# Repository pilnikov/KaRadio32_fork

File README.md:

# KaRadio32_fork
modifed files from karadio32 https://github.com/karawin/Ka-Radio32
for use with TTGO TM Music.

Since version 1.5. - end of support. For history only!
Please use original files with ttgotm.bin config and ST7789V (199) display.

Файлы для проекта Karadio32 https://github.com/karawin/Ka-Radio32
адаптированные под использование с платой TTGO TM Music
https://ru.aliexpress.com/item/Ttgo-2-4-PCM5102A-SD-ESP32-WiFi-Bluetooth/32848882218.html?spm=a2g0s.9042311.0.0.BYS264

Русский язык поддерживается!

Начиная с версии 1.5 потеряло актуальность. Теперь можно грузить оригинальную прошивку и специальный файл конфигурации ttgotm.bin из папочки \boards\build у автора(или тут). Дисплей в новых версиях - ST7789V (199)

Тут пока оставлю для истории. 

P.S. В папочку \boards буду складывать различные конфиги (под разные платы)
схема подключения в файликах с расширением .csv. Соответсвующие .csv бинарники лежат в подпапке \build. Грузить бинарник можно отдельно от основной прошивки по адресу 0x3a2000

пример 

строка P_TOUCH_CS,data,u8,16
означает, что пин CS тачскрина (для экранов с тачскринами, еще может обозначаться как t_cs) нужно подключить к GPIO16

строка P_BACKLIGHT,data,u8,255
означает, что управление подсветкой экрана не используется (значение 255) и экран будет светиться постоянно.

чтобы сделать .bin из .csv без msys
http://totel.kusto.com.ru:18888/karadio/

если установлен python:
1. заходите в папку с файлом вашей конфигурации. 
2. копируете туда файлик nvs_partition_gen.py. 
3. запускаете командную строку (cmd)
4. копируете строчку python nvs_partition_gen.py имя_конфига.csv имя_бинарника.bin 0x2000 (где вместо имя_конфига.csv подставляеете свой .csv (например ttgotm.csv (должен лежать в этой же папке)), а вместо имя_бинарника.bin произвольное имя файла которое потом будет заливаться (например build/ttgotm.bin (создаст подпапку /buld, а в неё положит файл ttgotm.bin ))

Теперь поддерживаются модули A1S от Aithinker!

Все исходники https://github.com/pilnikov/Ka_mod.
Бинарник собран при помощи Ninja & Cmake на базе IDF 4.1 (на IDF 5.x пока не работает)

Хорошая инструкция от Игоря Шерстюка (aka nadim)
https://www.drive2.ru/b/487463808323813881/

Еще инструкции от пользователя maleksm с форума Arduino 
http://arduino.ru/forum/proekty/wi-fi-internet-radio?page=104#comment-443847

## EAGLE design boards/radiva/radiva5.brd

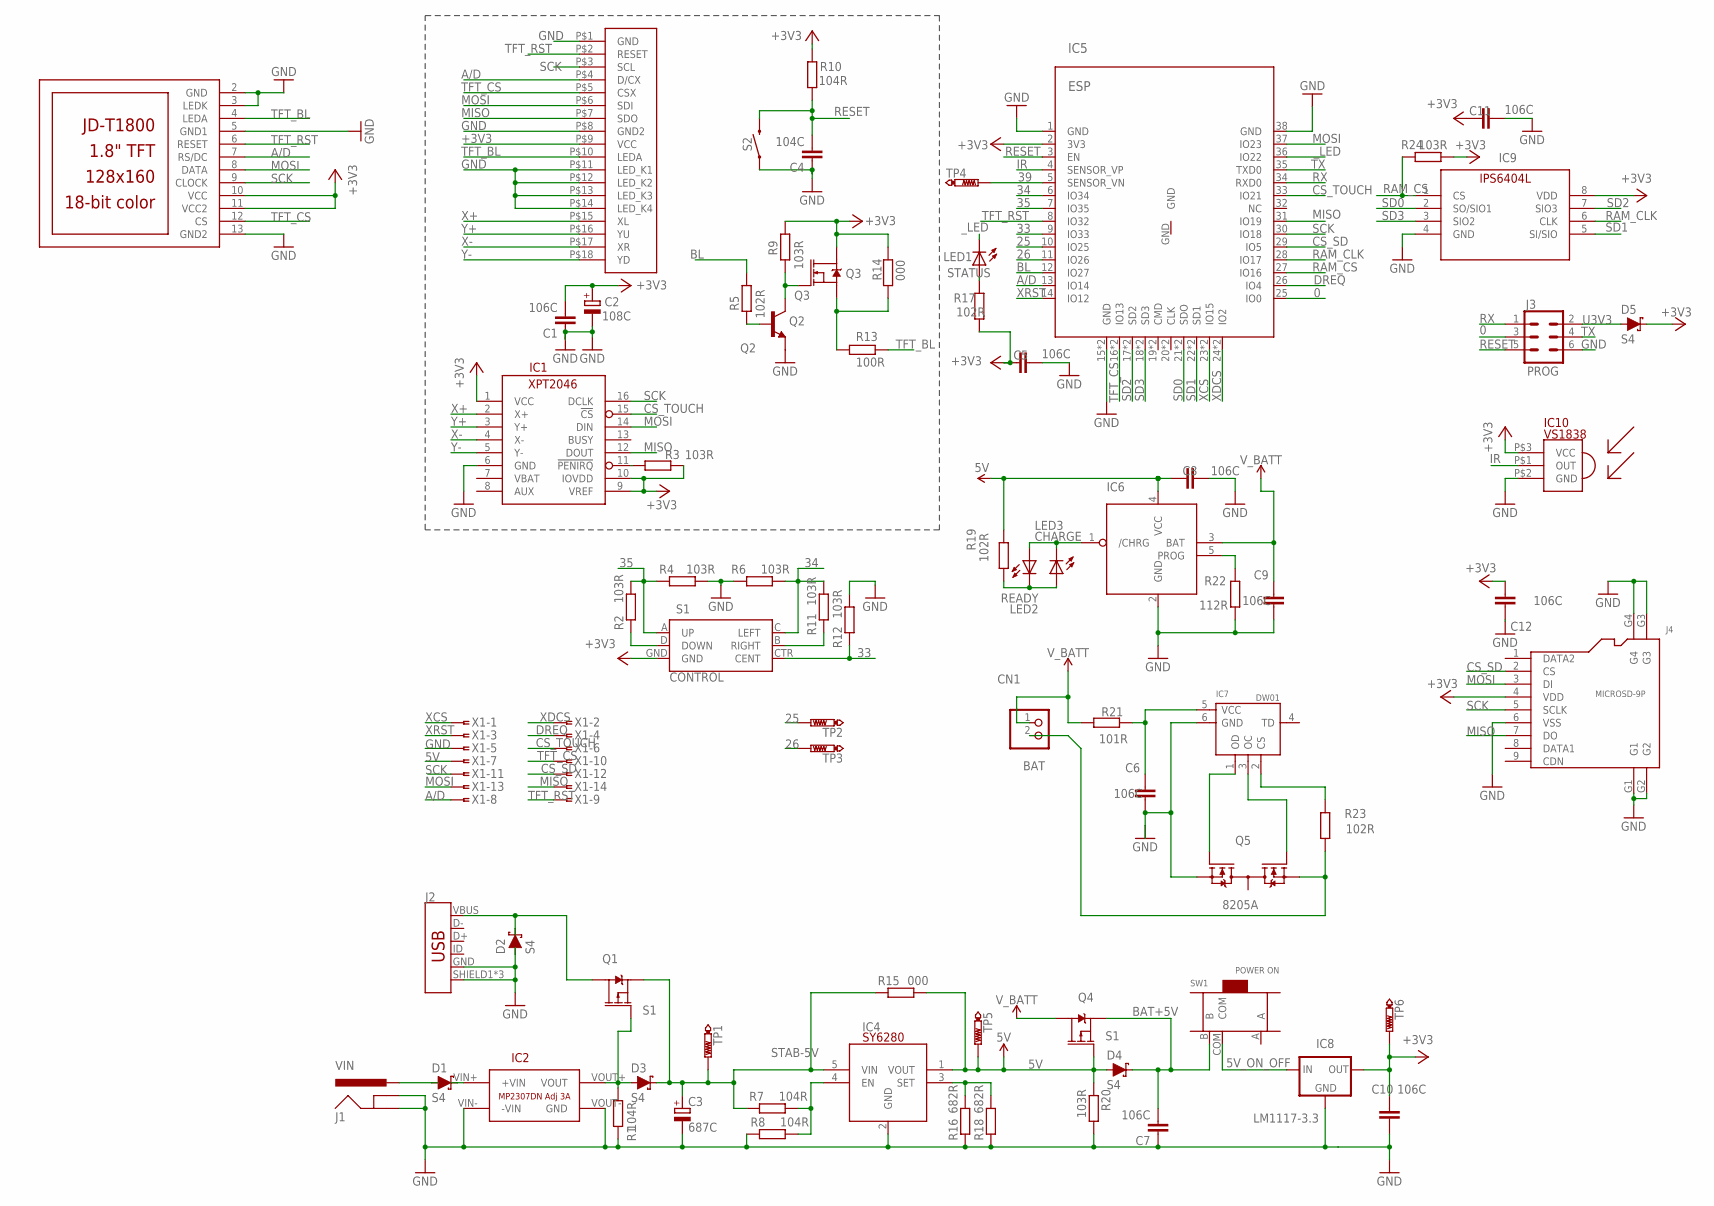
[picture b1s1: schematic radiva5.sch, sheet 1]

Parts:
C1, C5, C6, C7, C8, C9, C10, C11, C12: 106C; 0603-CAP
C2: 108C; E5-8,5
C3: 687C; E5-8,5
C4: 104C; 0603-CAP
CN1: BAT; JST-PH-2-SMT
D1, D2, D3, D4, D5: S4; SOD-323
IC1: TOUCH; TSSOP16-0.65-5X4.4MM
IC2: DC-DC 5V; DC-DC_MP2307DN
IC3: TFT-DISPLAY-2.8
IC4: SY6280; SOT23-5
IC5: ESP; ESP-WROOM-WROOVER-32
IC6: LT4; SOT23-5
IC7: DW01; SOT-23-6
IC8: LM1117-3.3; SOT223
IC9: SRAM; SO-08
IC10: VS1838; IR
J1: VIN; POWER_JACK_PTH_LOCK
J2: USB_MICRO-B_FEMALE-SMT; USB-B-MICRO-SMD
J3: PROG; 2X3
J4: MICROSD-9P; MICRO-SD9+4P-SMD-16.1X14.5X1.85MM
LCD1: TFT-DISPLAY-1.8; JD-T1800
LED1: STATUS; LED-0603
LED2: READY; LED-0603
LED3: CHARGE; LED-0603
Q1, Q4: S1; SOT23-3
Q2: Q2; SOT23-3
Q3: Q3; SOT23-3
Q5: 8205A; TSSOP-8
R1, R7, R8, R10: 104R; R0603
R2, R3, R4, R6, R9, R11, R12, R20, R24: 103R; R0603
R5, R17, R19, R23: 102R; R0603
R13: 100R; R0603
R14, R15: 000; R0603
R16, R18: 682R; R0603
R21: 101R; R0603
R22: 112R; R0603
S1: CONTROL; JOYSTICK_MINI
S2: RESET; TACTILE_SWITCH_PTH_8.0MM
SW1: POWER ON; SW7-SMD-L6.7X2.7X3.2MM
TP1: STAB 5V; P1-13
TP2: 25; B1,27
TP3: 26; B1,27
TP4: 39; B1,27
TP5: 5V; P1-13
TP6: 3.3V; P1-13
X1: FSIDE-14

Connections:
0: IC5.25 (IO0), J3.3
5V: C8.1, D4.+ (A), IC4.1 (VOUT), IC6.4 (VCC), Q4.1 (G), R15.2, R19.2, R20.1, TP5.TP, X1.7
5V_ON_OFF: IC8.3 (IN), SW1.COM
25: IC5.10 (IO25), TP2.TP
26: IC5.11 (IO26), TP3.TP
33: IC5.9 (IO33), R12.1, S1.CTR (CENT)
34: IC5.6 (IO34), R6.2, R11.2, S1.C (LEFT)
35: IC5.7 (IO35), R2.2, R4.1, S1.A (UP)
39: IC5.5 (SENSOR_VN), TP4.TP
+3V3: C1.2, C2.+, C5.1, C10.2, C11.1, C12.1, D5.- (C), IC1.1 (VCC), IC1.9 (VREF), IC1.10 (IOVDD), IC3.P$9 (VCC), IC5.2 (3V3), IC8.2 (OUT), IC8.4 (OUT), IC9.8 (VDD), IC10.P$3 (VCC), J4.4 (VDD), LCD1.10 (VCC), LCD1.11 (VCC2), Q3.3 (D), R3.1, R9.1, R10.1, R14.1, R17.1, R24.1, S1.GND, TP6.TP; also elsewhere on the board
A/D: IC3.P$4 (D/CX), IC5.13 (IO14), LCD1.7 (RS/DC), X1.8
BAT+5V: C7.2, D4.- (C), Q4.2 (S), SW1.B
BL: IC5.12 (IO27), R5.1
CHARGE: IC6.1 (/CHRG), LED2.A, LED3.C
CS_SD: IC5.29 (IO5), J4.2 (CS), X1.12
CS_TOUCH: IC1.15 (!CS), IC5.33 (IO21), X1.6
DREQ: IC5.26 (IO4), X1.4; also elsewhere on the board
FUSE_EN: IC4.4 (EN), R7.2, R8.1
FUSE_SET: IC4.3 (SET), R16.2, R18.2
GND: C1.1, C2.-, C3.-, C4.1, C5.2, C6.1, C7.1, C8.2, C9.1, C10.1, C11.2, C12.2, D2.+ (A), IC1.6 (GND), IC2.VIN- (-VIN), IC2.VOUT- (GND), IC3.P$1 (GND), IC3.P$8 (GND2), IC3.P$11 (LED_K1), IC3.P$12 (LED_K2), IC3.P$13 (LED_K3), IC3.P$14 (LED_K4), IC4.2 (GND), IC5.1 (GND), IC5.15 (GND), IC5.38 (GND), IC5.39 (GND), IC6.2 (GND), IC7.6 (GND), IC8.1 (GND), IC9.4 (GND), IC10.P$2 (GND), J1.GND, J1.GNDBREAK, J2.GND, J2.SHIELD1 (SHIELD), J2.SHIELD2 (SHIELD), J2.SHIELD3 (SHIELD), J3.6, J4.6 (VSS), J4.G1, J4.G2, J4.G3, J4.G4, LCD1.2 (GND), LCD1.3 (LEDK), LCD1.5 (GND1), LCD1.13 (GND2), Q2.2 (E), Q5.6 (S2), Q5.7 (S2), R1.2, R4.2, R6.1, R8.2, R12.2, R16.1, R18.1, R20.2, R22.1, S2.1, X1.5; also elsewhere on the board
ICHRG: IC6.5 (PROG), R22.2
IR: IC5.4 (SENSOR_VP), IC10.P$1 (OUT)
MISO: IC1.12 (DOUT), IC3.P$7 (SDO), IC5.31 (IO19), J4.7 (DO), X1.14; also elsewhere on the board
MOSI: IC1.14 (DIN), IC3.P$6 (SDI), IC5.37 (IO23), J4.3 (DI), LCD1.8 (DATA), X1.13; also elsewhere on the board
unnamed: Q2.3 (C), Q3.1 (G), R9.2
unnamed: Q3.2 (S), R13.1, R14.2
unnamed: Q2.1 (B), R5.2
unnamed: LED1.A, R17.2
unnamed: LED2.C, LED3.A, R19.1
unnamed: IC7.3 (OC), Q5.4 (G1)
unnamed: IC7.1 (OD), Q5.5 (G2)
unnamed: C6.2, IC7.5 (VCC), R21.2
unnamed: IC7.2 (CS), R23.2
unnamed: CN1.2 (1), Q5.2 (S1), Q5.3 (S1), R23.1
unnamed: IC1.11 (!PENIRQ), R3.2
unnamed: R11.1, S1.B (RIGHT)
unnamed: R2.1, S1.D (DOWN)
RAM_CLK: IC5.28 (IO17), IC9.6 (CLK)
RAM_CS: IC5.27 (IO16), IC9.1 (CS), R24.2
RESET: C4.2, IC5.3 (EN), J3.5, R10.2, S2.2
RX: IC5.34 (RXD0), J3.1
SCK: IC1.16 (DCLK), IC3.P$3 (SCL), IC5.30 (IO18), J4.5 (SCLK), LCD1.9 (CLOCK), X1.11; also elsewhere on the board
SD0: IC5.21 (SDO), IC5.45 (SDO), IC9.2 (SO/SIO1)
SD1: IC5.22 (SD1), IC5.46 (SD1), IC9.5 (SI/SIO)
SD2: IC5.17 (SD2), IC5.41 (SD2), IC9.7 (SIO3)
SD3: IC5.18 (SD3), IC5.42 (SD3), IC9.3 (SIO2)
STAB-5V: C3.+, D3.- (C), IC4.5 (VIN), Q1.2 (S), R7.1, R15.1, TP1.TP
STAB_5V_OUT: D3.+ (A), IC2.VOUT+ (VOUT), Q1.1 (G), R1.1
TFT_BL: IC3.P$10 (LEDA), LCD1.4 (LEDA), R13.2
TFT_CS: IC3.P$5 (CSX), IC5.16 (IO13), IC5.40 (IO13), LCD1.12 (CS), X1.10
TFT_RST: IC3.P$2 (RESET), IC5.8 (IO32), LCD1.6 (RESET), X1.9
TX: IC5.35 (TXD0), J3.4
U3V3: D5.+ (A), J3.2
VBUS: D2.- (C), J2.VBUS, Q1.3 (D)
VIN+: D1.+ (A), J1.PWR
V_BATT: C9.2, CN1.1 (2), IC6.3 (BAT), Q4.3 (D), R21.1
X+: IC1.2 (X+), IC3.P$15 (XL)
X-: IC1.4 (X-), IC3.P$17 (XR)
XCS: IC5.23 (IO15), IC5.47 (IO15), X1.1; also elsewhere on the board
XDCS: IC5.24 (IO2), IC5.48 (IO2), X1.2; also elsewhere on the board
XRST: IC5.14 (IO12), X1.3; also elsewhere on the board
Y+: IC1.3 (Y+), IC3.P$16 (YU)
Y-: IC1.5 (Y-), IC3.P$18 (YD)
_LED: IC5.36 (IO22), LED1.C
_VIN+: D1.- (C), IC2.VIN+ (+VIN)

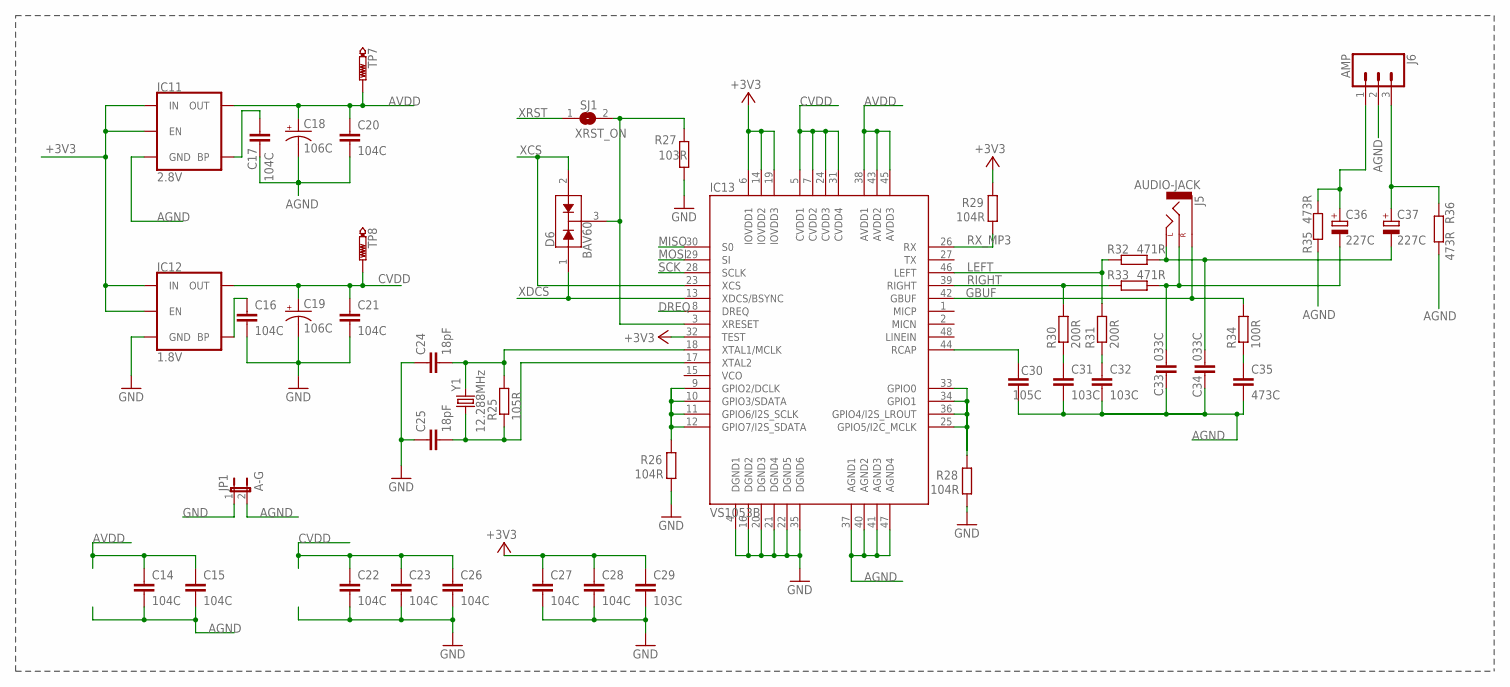
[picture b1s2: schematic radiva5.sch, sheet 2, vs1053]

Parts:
C14, C15, C16, C17, C20, C21, C22, C23, C26, C27, C28: 104C; 0603-CAP
C18, C19: 106C; EIA3216
C24, C25: 18pF; 0603-CAP
C29, C31, C32: 103C; 0603-CAP
C30: 105C; 0603-CAP
C33, C34: 033C; 0603-CAP
C35: 473C; 0603-CAP
C36, C37: 227C; E2,5-6
D6: BAV60; SOT23-3
IC11: 2.8V; SOT23-5
IC12: 1.8V; SOT23-5
IC13: VS1053B; LQFP-48
J5: AUDIO-JACK
J6: AMP; 1X03
JP1: A-G; SJ_2S
R25: 105R; R0603
R26, R28, R29: 104R; R0603
R27: 103R; R0603
R30, R31: 200R; R0603
R32, R33: 471R; R0603
R34: 100R; R0603
R35, R36: 473R; R0603
SJ1: XRST_ON; SJ
TP7: 2.8V; B1,27
TP8: 1.8V; B1,27
Y1: 12.288MHz; HC49U

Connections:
+3V3: C27.1, C28.1, C29.1, IC11.1 (IN), IC11.3 (EN), IC12.1 (IN), IC12.3 (EN), IC13.6 (IOVDD1), IC13.14 (IOVDD2), IC13.19 (IOVDD3), IC13.32 (TEST), R29.2; also elsewhere on the board
AGND: C14.2, C15.2, C17.2, C18.C (-), C20.2, C30.1, C31.2, C32.2, C33.2, C34.2, C35.2, IC11.2 (GND), IC13.37 (AGND1), IC13.40 (AGND2), IC13.41 (AGND3), IC13.47 (AGND4), J6.2, JP1.2, R35.2, R36.1
AMP_L: C36.+, J6.1, R35.1
AMP_R: C37.+, J6.3, R36.2
AVDD: C14.1, C15.1, C18.A (+), C20.1, IC11.5 (OUT), IC13.38 (AVDD1), IC13.43 (AVDD2), IC13.45 (AVDD3), TP7.TP
CVDD: C19.A (+), C21.1, C22.1, C23.1, C26.1, IC12.5 (OUT), IC13.5 (CVDD1), IC13.7 (CVDD2), IC13.24 (CVDD3), IC13.31 (CVDD4), TP8.TP
DREQ: IC13.8 (DREQ); also elsewhere on the board
GBUF: IC13.42 (GBUF), J5.P$3 (SLEEVE), J5.P$4 (SLEEVE), R34.2
GND: C16.2, C19.C (-), C21.2, C22.2, C23.2, C24.1, C25.1, C26.2, C27.2, C28.2, C29.2, IC12.2 (GND), IC13.4 (DGND1), IC13.16 (DGND2), IC13.20 (DGND3), IC13.21 (DGND4), IC13.22 (DGND5), IC13.35 (DGND6), JP1.1, R26.1, R27.1, R28.1; also elsewhere on the board
GPIO_0: IC13.25 (GPIO5/I2C_MCLK), IC13.33 (GPIO0), IC13.34 (GPIO1), IC13.36 (GPIO4/I2S_LROUT), R28.2
GPIO_2: IC13.9 (GPIO2/DCLK), IC13.10 (GPIO3/SDATA), IC13.11 (GPIO6/I2S_SCLK), IC13.12 (GPIO7/I2S_SDATA), R26.2
HP_L: C33.1, C36.-, J5.P$2 (RIGHT), R33.1
HP_R: C34.1, C37.-, J5.P$1 (LEFT), J5.P$5 (LEFT), R32.1
LEFT: IC13.46 (LEFT), R31.2, R32.2
MISO: IC13.30 (S0); also elsewhere on the board
MOSI: IC13.29 (SI); also elsewhere on the board
unnamed: C17.1, IC11.4 (BP)
unnamed: C16.1, IC12.4 (BP)
unnamed: C32.1, R31.1
unnamed: C31.1, R30.1
unnamed: C35.1, R34.1
RCAP: C30.2, IC13.44 (RCAP)
RIGHT: IC13.39 (RIGHT), R30.2, R33.2
RX_MP3: IC13.26 (RX), R29.1
SCK: IC13.28 (SCLK); also elsewhere on the board
XCS: D6.2 (A2), IC13.23 (XCS); also elsewhere on the board
XDCS: D6.1 (A1), IC13.13 (XDCS/BSYNC); also elsewhere on the board
XRESET: D6.3 (COM), IC13.3 (XRESET), R27.2, SJ1.2
XRST: SJ1.1; also elsewhere on the board
XTAL+: C25.2, IC13.17 (XTAL2), R25.1, Y1.1
XTAL-: C24.2, IC13.18 (XTAL1/MCLK), R25.2, Y1.2

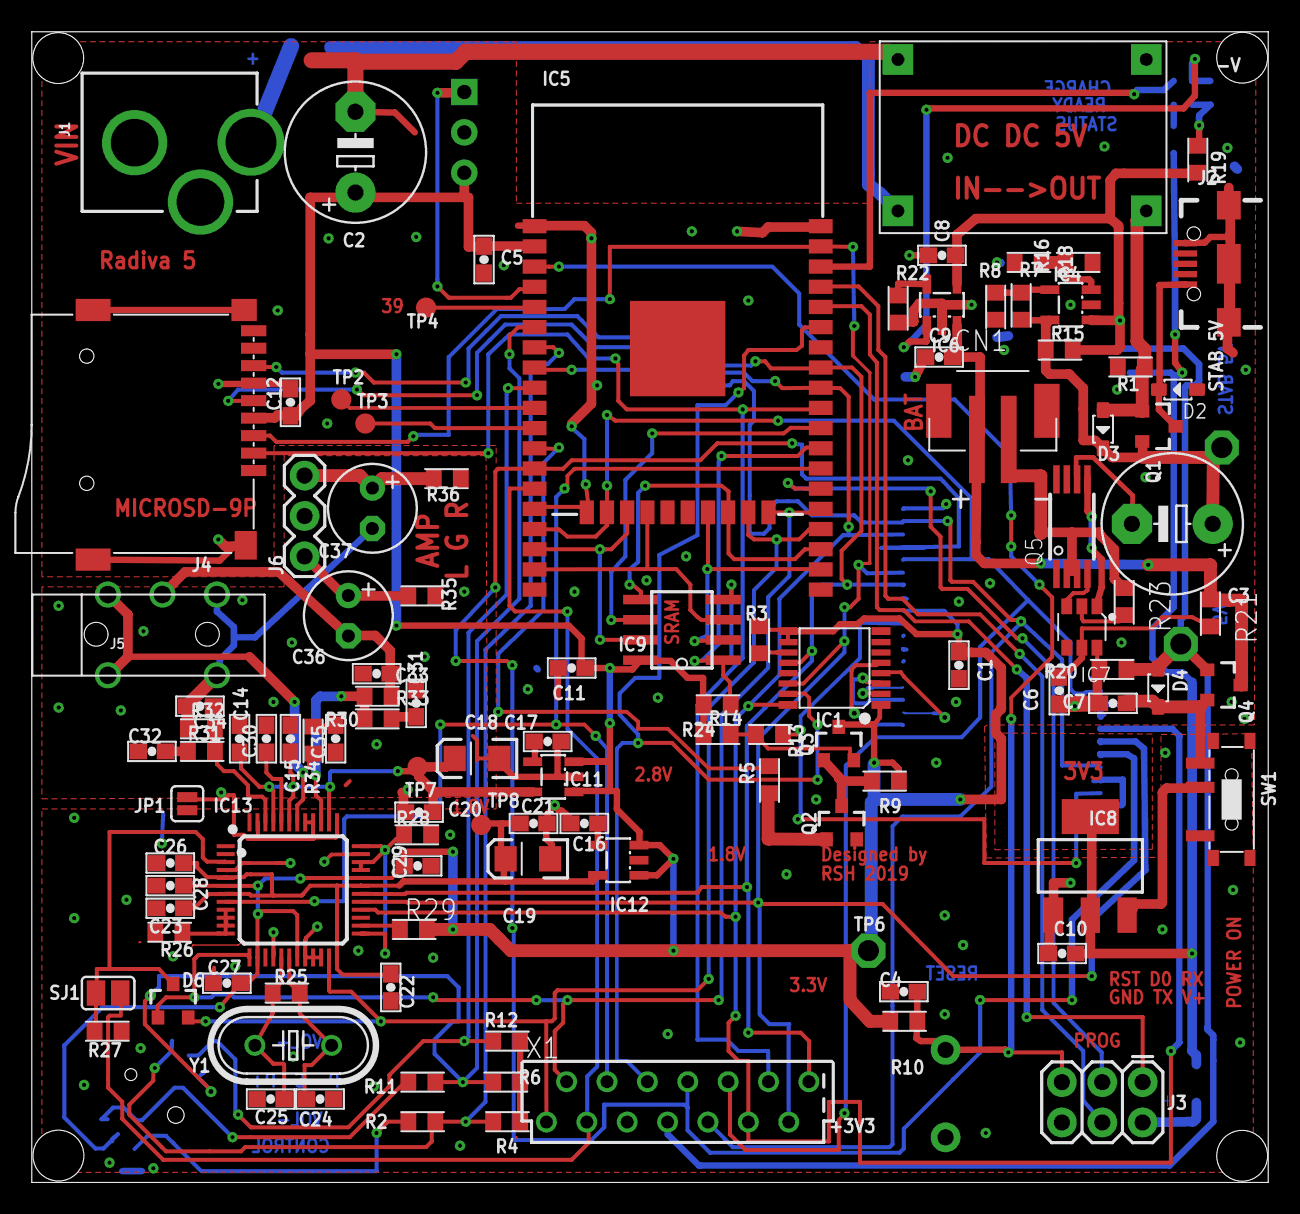
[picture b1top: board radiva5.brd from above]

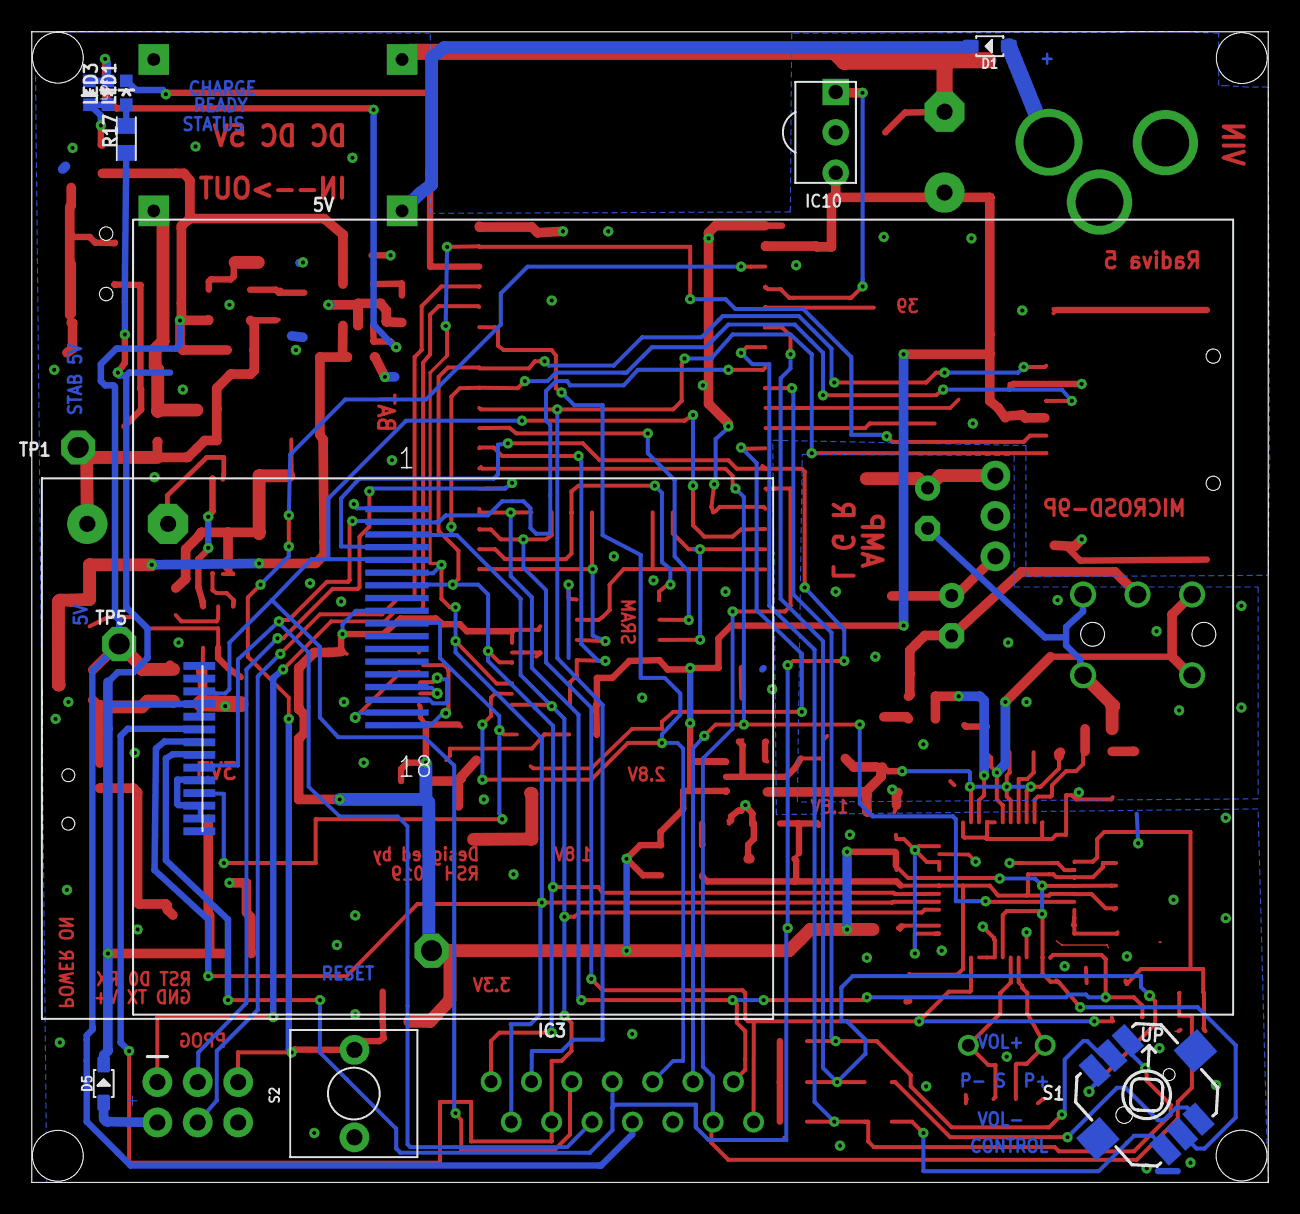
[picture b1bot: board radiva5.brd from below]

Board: 2 copper layers, 77.8 x 72.4 mm, 122 parts (13 on the bottom side), 87 nets.

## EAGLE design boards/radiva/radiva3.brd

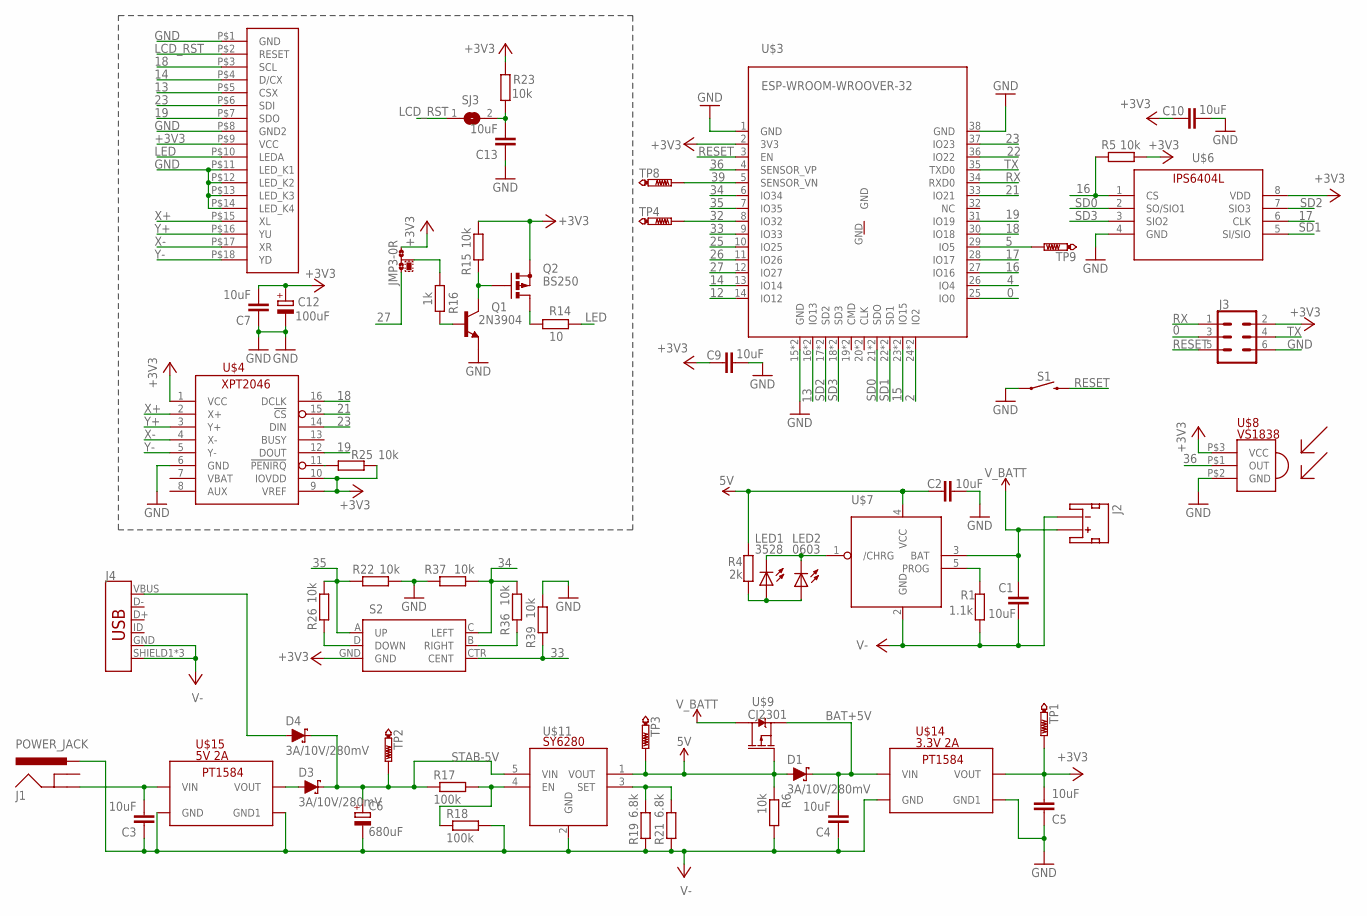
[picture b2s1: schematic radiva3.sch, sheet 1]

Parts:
C1, C2, C3, C4, C5, C7, C9, C10, C13: 10uF; C0805
C6: 680uF; E5-8,5
C12: 100uF; E5-8,5
D1, D3, D4: 3A/10V/280mV; SOD-323
J1: POWER_JACK; POWER_JACK_PTH
J2: JST_2MM_MALE; JST-2-SMD
J3: CONN_03X22X3_SILK_MALE_PTH; 2X3
J4: USB_MICRO-B_FEMALE-SMT; USB-B-MICRO-SMD
JMP3: 0R-JUMPC; C0R-JMP
LED1: 3528; KA-3528ASYC
LED2: 0603; LED-0603
Q1: 2N3904; TO92
Q2: BS250; SOT54E
R1: 1.1k; R0402
R4: 2k; R0402
R5, R6, R15, R22, R23, R25, R26, R36, R37, R39: 10k; R0402
R14: 10; R0402
R16: 1k; R0402
R17, R18: 100k; R0402
R19, R21: 6.8k; R0402
S1: MOMENTARY-SWITCH-SPST-PTH-6.0MM; TACTILE_SWITCH_PTH_6.0MM
S2: JOYSTICK_MINI
SJ3: SJ
TP1, TP2, TP3: PTR1PAD1-13; P1-13
TP4, TP8, TP9: PTR1B1,27; B1,27
U$3: ESP-WROOM-WROOVER-32
U$4: XPT2046; TSSOP16-0.65-5X4.4MM
U$6: IPS6404L-SQ-SPN; SO-08
U$7: TP4054; SOT23-5
U$8: VS1838; IR
U$9: CJ2301; SOT23-3
U$10: TFT-DISPLAY-2.8
U$11: SY6280; SOT23-5
U$14: 3.3V 2A; DC-DC_PT1584
U$15: 5V 2A; DC-DC_PT1584

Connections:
0: J3.3, U$3.25 (IO0)
2: U$3.24 (IO2), U$3.48 (IO2); also elsewhere on the board
4: U$3.26 (IO4); also elsewhere on the board
5: TP9.TP, U$3.29 (IO5)
5V: C2.1, D1.A, R4.2, R6.1, TP3.TP, U$7.4 (VCC), U$9.1 (G), U$11.1 (VOUT)
12: U$3.14 (IO12); also elsewhere on the board
13: U$3.16 (IO13), U$3.40 (IO13), U$10.P$5 (CSX)
14: U$3.13 (IO14), U$10.P$4 (D/CX)
15: U$3.23 (IO15), U$3.47 (IO15); also elsewhere on the board
16: R5.2, U$3.27 (IO16), U$6.1 (CS)
17: U$3.28 (IO17), U$6.6 (CLK)
18: U$3.30 (IO18), U$4.16 (DCLK), U$10.P$3 (SCL); also elsewhere on the board
19: U$3.31 (IO19), U$4.12 (DOUT), U$10.P$7 (SDO); also elsewhere on the board
21: U$3.33 (IO21), U$4.15 (!CS)
22: U$3.36 (IO22); also elsewhere on the board
23: U$3.37 (IO23), U$4.14 (DIN), U$10.P$6 (SDI); also elsewhere on the board
25: U$3.10 (IO25); also elsewhere on the board
26: U$3.11 (IO26); also elsewhere on the board
27: JMP3.1, U$3.12 (IO27)
32: TP4.TP, U$3.8 (IO32)
33: R39.1, S2.CTR (CENT), U$3.9 (IO33)
34: R36.2, R37.2, S2.C (LEFT), U$3.6 (IO34)
35: R22.1, R26.2, S2.A (UP), U$3.7 (IO35)
36: U$3.4 (SENSOR_VP), U$8.P$1 (OUT)
39: TP8.TP, U$3.5 (SENSOR_VN)
+3V3: C5.2, C7.2, C9.1, C10.1, C12.+, J3.2, JMP3.3, Q2.S, R5.1, R15.1, R23.1, R25.1, S2.GND, TP1.TP, U$3.2 (3V3), U$4.1 (VCC), U$4.9 (VREF), U$4.10 (IOVDD), U$6.8 (VDD), U$8.P$3 (VCC), U$10.P$9 (VCC), U$14.P$4 (VOUT), U$14.P$8 (VOUT); also elsewhere on the board
BAT+5V: C4.2, D1.C, U$9.2 (S), U$14.P$1 (VIN), U$14.P$5 (VIN); also elsewhere on the board
GND: C2.2, C5.1, C7.1, C9.2, C10.2, C12.-, C13.1, J3.6, Q1.3 (E), R22.2, R37.1, R39.2, S1.1, U$3.1 (GND), U$3.15 (GND), U$3.38 (GND), U$3.39 (GND), U$4.6 (GND), U$6.4 (GND), U$8.P$2 (GND), U$10.P$1 (GND), U$10.P$8 (GND2), U$10.P$11 (LED_K1), U$10.P$12 (LED_K2), U$10.P$13 (LED_K3), U$10.P$14 (LED_K4), U$14.P$3 (GND1), U$14.P$7 (GND1); also elsewhere on the board
LCD_RST: SJ3.1, U$10.P$2 (RESET)
LED: R14.2, U$10.P$10 (LEDA)
unnamed: Q1.1 (C), Q2.G, R15.2
unnamed: Q2.D, R14.1
unnamed: Q1.2 (B), R16.2
unnamed: LED1.A, LED2.A, R4.1
unnamed: C3.2, J1.GND, U$15.P$1 (VIN), U$15.P$5 (VIN)
unnamed: LED1.C, LED2.C, U$7.1 (/CHRG)
unnamed: R1.2, U$7.5 (PROG)
unnamed: C13.2, R23.2, SJ3.2
unnamed: JMP3.2, R16.1
unnamed: R17.2, R18.1, U$11.4 (EN)
unnamed: R19.2, R21.2, U$11.3 (SET)
unnamed: D3.A, U$15.P$4 (VOUT), U$15.P$8 (VOUT)
unnamed: R25.2, U$4.11 (!PENIRQ)
unnamed: D4.A, J4.VBUS
unnamed: R36.1, S2.B (RIGHT)
unnamed: R26.1, S2.D (DOWN)
RESET: J3.5, S1.3 (2), U$3.3 (EN)
RX: J3.1, U$3.34 (RXD0)
SD0: U$3.21 (SDO), U$3.45 (SDO), U$6.2 (SO/SIO1)
SD1: U$3.22 (SD1), U$3.46 (SD1), U$6.5 (SI/SIO)
SD2: U$3.17 (SD2), U$3.41 (SD2), U$6.7 (SIO3)
SD3: U$3.18 (SD3), U$3.42 (SD3), U$6.3 (SIO2)
STAB-5V: C6.+, D3.C, D4.C, R17.1, TP2.TP, U$11.5 (VIN)
TX: J3.4, U$3.35 (TXD0)
V-: C1.1, C3.1, C4.1, C6.-, J1.PWR, J2.1 (-), J4.GND, J4.SHIELD1 (SHIELD), J4.SHIELD2 (SHIELD), J4.SHIELD3 (SHIELD), R1.1, R6.2, R18.2, R19.1, R21.1, U$7.2 (GND), U$11.2 (GND), U$14.P$2 (GND), U$14.P$6 (GND), U$15.P$2 (GND), U$15.P$3 (GND1), U$15.P$6 (GND), U$15.P$7 (GND1)
V_BATT: C1.2, J2.2 (+), U$7.3 (BAT), U$9.3 (D)
X+: U$4.2 (X+), U$10.P$15 (XL)
X-: U$4.4 (X-), U$10.P$17 (XR)
Y+: U$4.3 (Y+), U$10.P$16 (YU)
Y-: U$4.5 (Y-), U$10.P$18 (YD)

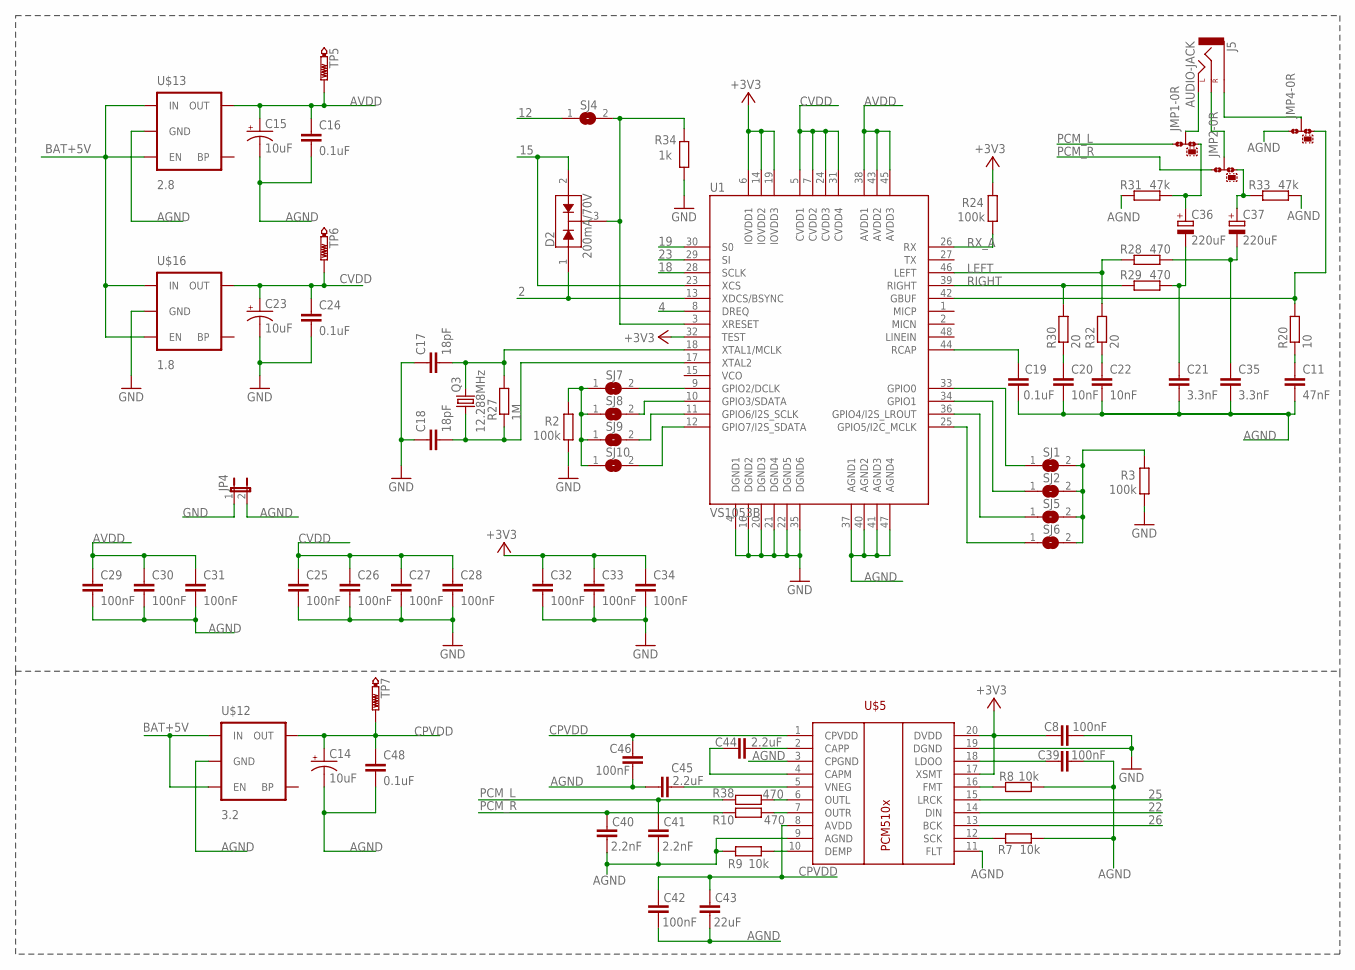
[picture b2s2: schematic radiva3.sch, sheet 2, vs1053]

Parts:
C8, C25, C26, C27, C28, C29, C30, C31, C32, C33, C34, C39, C42, C46: 100nF; 0402-CAP
C11: 47nF; 0402-CAP
C14, C15, C23: 10uF; EIA3216
C16, C19, C24, C48: 0.1uF; 0402-CAP
C17, C18: 18pF; 0402-CAP
C20, C22: 10nF; 0402-CAP
C21, C35: 3.3nF; 0402-CAP
C36, C37: 220uF; E2,5-6
C40, C41: 2.2nF; 0402-CAP
C43: 22uF; 0805
C44, C45: 2.2uF; 0603-CAP
D2: 200mA/70V; SOT23-3
J5: AUDIO-JACK
JMP1, JMP2, JMP4: 0R-JUMPC; C0R-JMP
JP4: JUMPER-2SMD-NC; SJ_2S
Q3: 12.288MHz; HC49U
R2, R3, R24: 100k; R0402
R7, R8, R9: 10k; R0402
R10, R28, R29, R38: 470; R0402
R20: 10; R0402
R27: 1M; R0402
R30, R32: 20; R0402
R31, R33: 47k; R0402
R34: 1k; R0402
SJ1, SJ2, SJ4, SJ5, SJ6, SJ7, SJ8, SJ9, SJ10: SJ
TP5, TP6, TP7: PTR1B1,27; B1,27
U1: VS1053B; LQFP-48
U$5: PCM510X; SSOP20
U$12: 3.2; SC70
U$13: 2.8; SC70
U$16: 1.8; SC70

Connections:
2: D2.1 (A1), U1.13 (XDCS/BSYNC); also elsewhere on the board
4: U1.8 (DREQ); also elsewhere on the board
12: SJ4.1; also elsewhere on the board
15: D2.2 (A2), U1.23 (XCS); also elsewhere on the board
18: U1.28 (SCLK); also elsewhere on the board
19: U1.30 (S0); also elsewhere on the board
22: U$5.14 (DIN); also elsewhere on the board
23: U1.29 (SI); also elsewhere on the board
25: U$5.15 (LRCK); also elsewhere on the board
26: U$5.13 (BCK); also elsewhere on the board
+3V3: C8.1, C32.1, C33.1, C34.1, R24.2, U1.6 (IOVDD1), U1.14 (IOVDD2), U1.19 (IOVDD3), U1.32 (TEST), U$5.17 (XSMT), U$5.20 (DVDD); also elsewhere on the board
AGND: C11.2, C14.C (-), C15.C (-), C16.2, C19.1, C20.2, C21.2, C22.2, C29.2, C30.2, C31.2, C35.2, C39.2, C40.2, C41.2, C42.2, C43.2, C45.1, C46.1, C48.2, JMP4.1, JP4.2, R7.2, R8.2, R9.1, R31.2, R33.1, U1.37 (AGND1), U1.40 (AGND2), U1.41 (AGND3), U1.47 (AGND4), U$5.3 (CPGND), U$5.9 (AGND), U$5.11 (FLT), U$12.2 (GND), U$13.2 (GND)
AVDD: C15.A (+), C16.1, C29.1, C30.1, C31.1, TP5.TP, U1.38 (AVDD1), U1.43 (AVDD2), U1.45 (AVDD3), U$13.5 (OUT)
BAT+5V: U$12.1 (IN), U$12.3 (EN), U$13.1 (IN), U$13.3 (EN), U$16.1 (IN), U$16.3 (EN); also elsewhere on the board
CPVDD: C14.A (+), C42.1, C43.1, C46.2, C48.1, TP7.TP, U$5.1 (CPVDD), U$5.8 (AVDD), U$12.5 (OUT)
CVDD: C23.A (+), C24.1, C25.1, C26.1, C27.1, C28.1, TP6.TP, U1.5 (CVDD1), U1.7 (CVDD2), U1.24 (CVDD3), U1.31 (CVDD4), U$16.5 (OUT)
GBUF: JMP4.3, R20.2, U1.42 (GBUF)
GND: C8.2, C17.1, C18.1, C23.C (-), C24.2, C25.2, C26.2, C27.2, C28.2, C32.2, C33.2, C34.2, JP4.1, R2.1, R3.1, R34.1, U1.4 (DGND1), U1.16 (DGND2), U1.20 (DGND3), U1.21 (DGND4), U1.22 (DGND5), U1.35 (DGND6), U$5.19 (DGND), U$16.2 (GND); also elsewhere on the board
LEFT: R28.2, R32.2, U1.46 (LEFT)
unnamed: R8.1, U$5.16 (FMT)
unnamed: SJ7.2, U1.9 (GPIO2/DCLK)
unnamed: SJ1.1, U1.33 (GPIO0)
unnamed: SJ2.1, U1.34 (GPIO1)
unnamed: C39.1, U$5.18 (LDOO)
unnamed: R7.1, U$5.12 (SCK)
unnamed: SJ5.1, U1.36 (GPIO4/I2S_LROUT)
unnamed: R3.2, SJ1.2, SJ2.2, SJ5.2, SJ6.2
unnamed: C21.1, C36.-, R29.1
unnamed: C35.1, C37.-, R28.1
unnamed: C17.2, Q3.2, R27.2, U1.18 (XTAL1/MCLK)
unnamed: J5.P$1 (LEFT), J5.P$5 (LEFT), JMP1.2
unnamed: C18.2, Q3.1, R27.1, U1.17 (XTAL2)
unnamed: C19.2, U1.44 (RCAP)
unnamed: C22.1, R32.1
unnamed: J5.P$2 (RIGHT), JMP2.2
unnamed: C20.1, R30.1
unnamed: C11.1, R20.1
unnamed: C37.+, JMP2.3, R33.2
unnamed: C36.+, JMP1.3, R31.1
unnamed: SJ6.1, U1.25 (GPIO5/I2C_MCLK)
unnamed: SJ10.2, U1.12 (GPIO7/I2S_SDATA)
unnamed: SJ9.2, U1.11 (GPIO6/I2S_SCLK)
unnamed: SJ8.2, U1.10 (GPIO3/SDATA)
unnamed: R9.2, U$5.10 (DEMP)
unnamed: R10.2, U$5.7 (OUTR)
unnamed: R38.2, U$5.6 (OUTL)
unnamed: C45.2, U$5.5 (VNEG)
unnamed: C44.2, U$5.2 (CAPP)
unnamed: C44.1, U$5.4 (CAPM)
unnamed: J5.P$3 (SLEEVE), J5.P$4 (SLEEVE), JMP4.2
unnamed: R2.2, SJ7.1, SJ8.1, SJ9.1, SJ10.1
PCM_L: C41.1, JMP1.1, R38.1
PCM_R: C40.1, JMP2.1, R10.1
RIGHT: R29.2, R30.2, U1.39 (RIGHT)
RX_A: R24.1, U1.26 (RX)
XRESET: D2.3 (COM), R34.2, SJ4.2, U1.3 (XRESET)

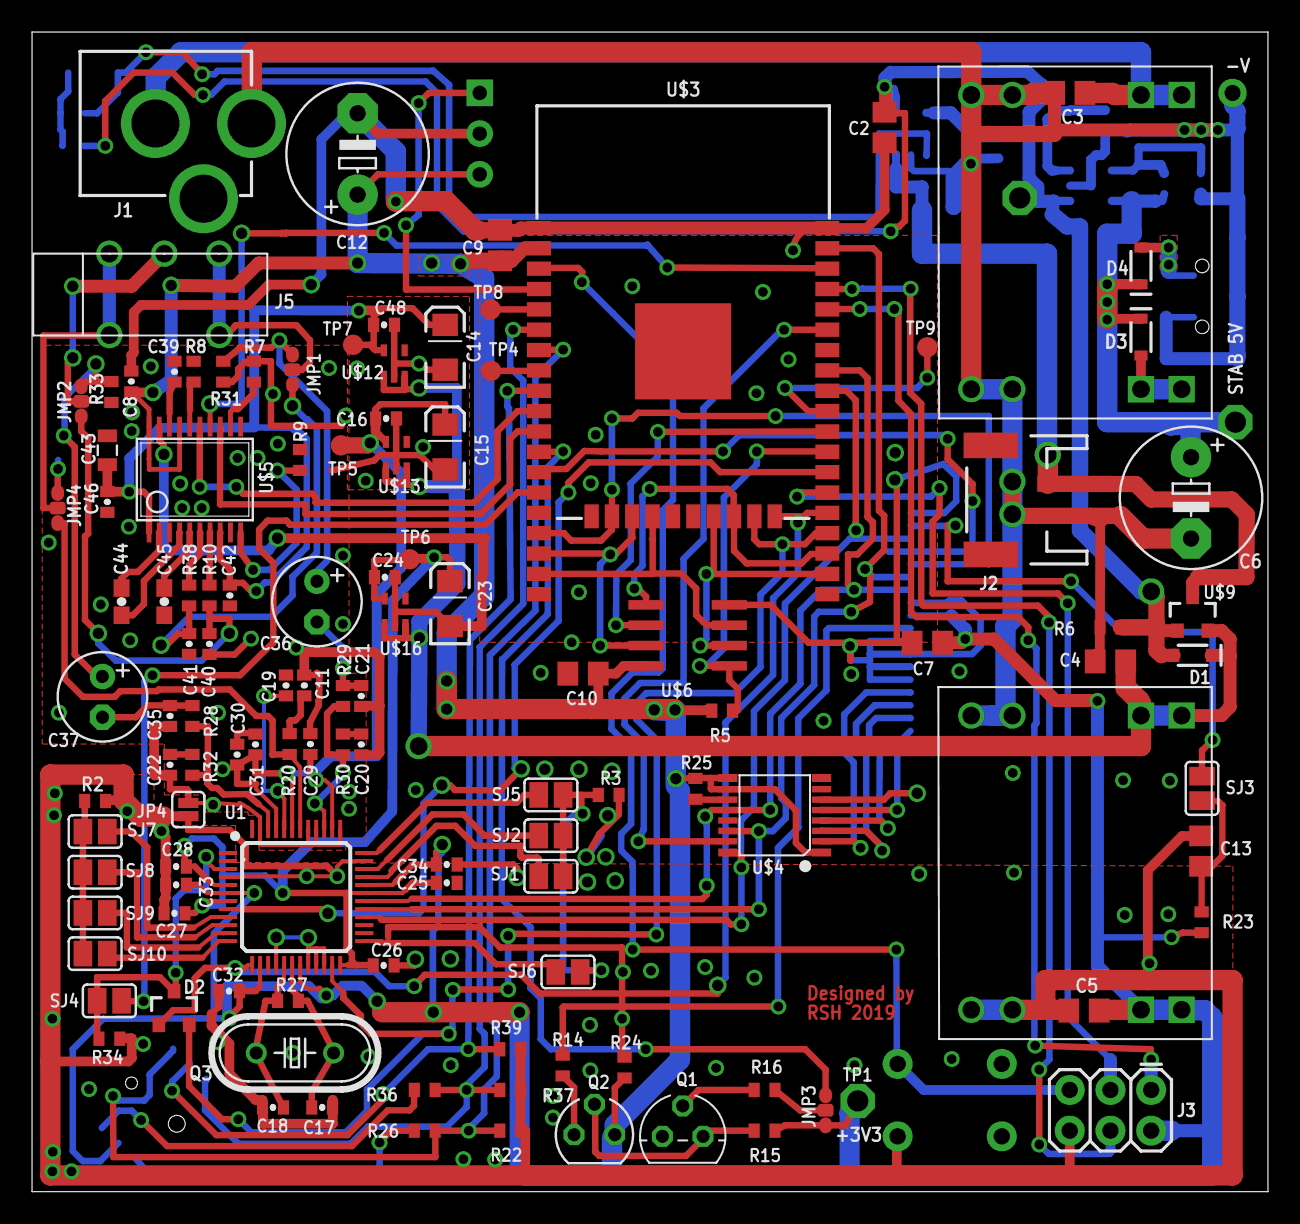
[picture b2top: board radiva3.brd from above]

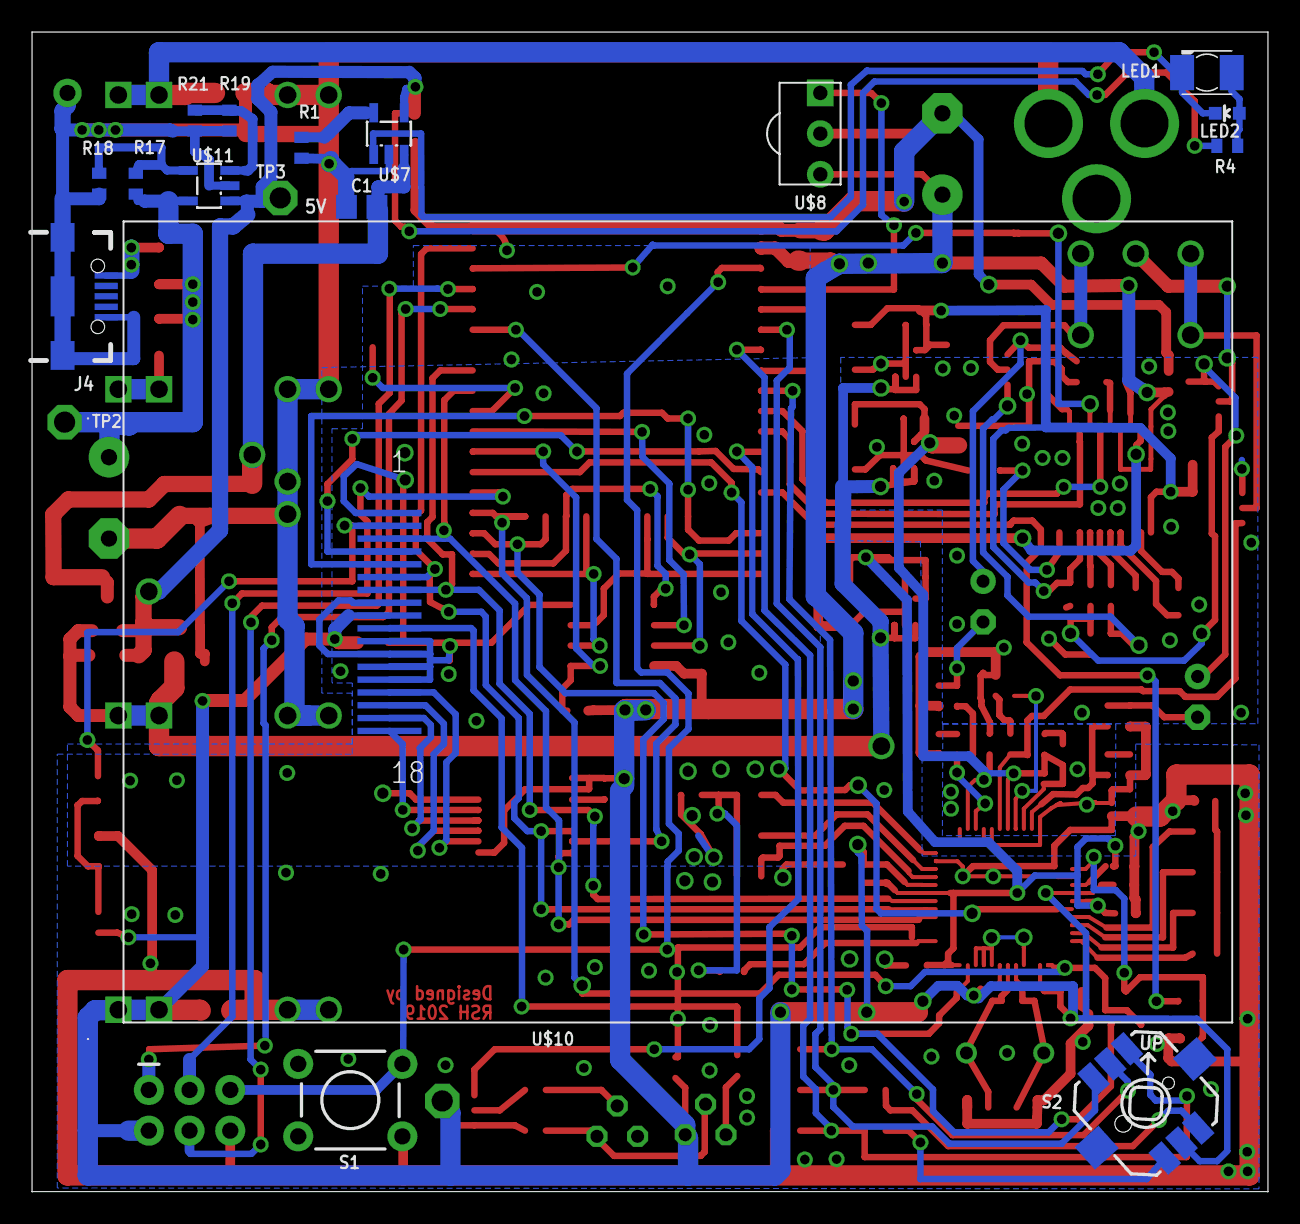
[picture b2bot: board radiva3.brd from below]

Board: 2 copper layers, 77.0 x 72.3 mm, 136 parts (18 on the bottom side), 103 nets.

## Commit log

2018-03-14 First add
2018-07-28 Add little instructions
2018-08-27 For replaced
2018-08-27 Add tool for work with fonts in ucglib
2018-08-27 add example
2018-08-28 Update to newest ver.
2018-08-28 For compartible with old i2s
2018-08-28 rus font -
2018-08-30 upd_font
2018-08-31 update font rus
2018-08-31 support cyrilic
2018-09-03 little bug fix
2018-09-03 update0309
2018-09-03 buf gix
2018-09-03 update 0309
2018-09-15 Now buttons work!
2018-09-15 Add buttons
2018-09-15 Beta 1.3R2
2018-09-17 Uipdate to 1.3.R1
2018-11-27 End of support
2019-01-14 adding config for my ttgo
2019-01-27 modifed
2019-01-27 last modifed
2019-01-27 Add doc
2019-01-27 Add touch board
2019-02-05 modified 05.02
2019-02-18 add some files
2019-02-19 add standard_button
2019-02-20 add new
2019-02-20 modified board for 1.9r2
2019-02-22 add ttgo ts
2019-02-22 Add ttgo ts doc
2019-02-22 Modified docs
2019-02-24 little modify ttgo tm conf
2019-02-26 add joystick
2019-04-03 03042019
2019-04-03 little
2019-04-03 add priint
2019-04-03 add pictures
2019-04-17 Add files via upload
    add blank.bin
2019-04-19 Add new version of pcb
2019-04-21 update vs_only
2019-04-25 Add test vs1053
2019-05-03 correct vs_only
2019-05-04 fix bug on radiva5 brd
2019-06-26 add radiva8
2019-07-05 add radiva 5.1
2019-07-05 add shematic
2019-09-12 support idf 4.1
2019-09-13 radiva 5.2
2019-09-28 New mod 1.9.5
2019-10-04 add online generator
2019-10-24 litle bug fix in bin files 1.9.5 mod
2019-10-25 new web page
2019-10-30 new ver of mod 1.9.5 .bin
2019-11-06 bin, test & playlist upd
2019-11-21 full working version
2019-12-04 last update
2019-12-12 update bin
2019-12-27 add pin test
2020-01-10 Update README.md
    add instructions from forum
2020-01-14 MOdify tests
2020-06-28 upd boards
2020-08-09 add radiva 835
2020-12-02 new config
2021-11-24 remove trash

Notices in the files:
parts and their libraries:
SparkFun-DiscreteSemi: Licensing: Creative Commons ShareAlike 4.0 International - https://creativecommons.org/licenses/by-sa/4.0
